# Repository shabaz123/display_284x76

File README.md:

# Display\_284x76

This repository contains KiCad files for an 81 x 29 mm circuit board which contains a 284x76 pixel TFT screen, six buttons and a rotary encoder.

The interface is via either a 20-pin DIL header, or 20-way 1mm-pitch flat flex cable (FFC), to any microcontroller of choice.

The board requires a 5V supply (4.4V to 5.5V should work) at 20 mA for the backlight driver, and a 3.3V 20mA supply for the TFT driver. All signals (SPI and the PWM input) use 3.3V logic levels.

The TFT is part code ER-TFT2.25-1 from BuyDisplay. It contains a ST7789P3 display controller.

# Circuit Diagram

# Pinout

Both the 20-way DIL header and the 20-way FFC connector have the same pinout:

<!-- info: table: widths="13% 87%" -->

| Pin | Description         |
| :-- | :------------------ |
| 1   | GND                 |
| 2   | 5V Input (4.4-5.5V) |
| 3   | SW6'                |
| 4   | SW6                 |
| 5   | SW1                 |
| 6   | SW2                 |
| 7   | SW3                 |
| 8   | SW4                 |
| 9   | SW5                 |
| 10  | ENC\_SW             |
| 11  | ENC\_B              |
| 12  | ENC\_A              |
| 13  | \*TFT\_CS           |
| 14  | TFT\_SCLK           |
| 15  | TFT\_MOSI           |
| 16  | LED\_PWM            |
| 17  | \*TFT\_RESET        |
| 18  | TFT\_D/\*C          |
| 19  | 3.3V Input          |
| 20  | GND                 |

# Enclosure

A possible enclosure is Hammond 1593W. See the front-panel folder for a KiCad project for this example front panel:

M2 spacers of height 6 mm should be suitable for attaching to the display board. 
The button holes are 5.2 mm diameter, which is suitable for "A30 button caps" which are 4.6 mm diameter and intended for B3F-1050 tact switches with a 2.4x2.4 mm square actuator. If you're using different buttons or caps, then you'll likely need to modify the holes in the KiCad files.

# Parts List

<!-- info: table: widths="11% 10% 21% 58%" -->

| Ref     | Qty | Value          | Description                                      |
| :------ | :-- | :------------- | :----------------------------------------------- |
| C1, C2  | 2   | 10n            | Capacitor 0805                                   |
| C3      | 1   | 10u 10V        | Capacitor Tant Case B                            |
| C4-C6   | 3   | 10u 10V        | Capacitor 0805 X7R                               |
| R1-R4   | 4   | 10k            | Resistor 0805                                    |
| R5      | 1   | 47k            | Resistor 0805                                    |
| R6      | 1   | 1k             | Resistor 0805                                    |
| R7      | 1   | 100k           | Resistor 0805                                    |
| R8      | 1   | 20k            | Resistor 0805                                    |
| R9      | 1   | 10R            | Resistor 0805                                    |
| L1      | 1   | 2.2uH          | Inductor 4x4mm 2A 50 mOhm: YNR4026-2R2M          |
| U3      | 1   | TLV62569DBV    | Buck Regulator SOT-23-5                          |
| FB1     | 1   | BLM21AG121SH1D | Ferrite Bead 0805                                |
| ENC1    | 1   | ENC12E         | Rotary Encoder                                   |
| SW1-SW6 | 6   | B3F-1050       | 6x6 B3F or Kailh Mute or E-Switch 5.8x5.8 or 7x7 |
| LCD1    | 1   | ER-TFT2.25-1   | 76x284 ST7789P3 TFT LCD Screen                   |
| LCDCONN | 1   | FFC2B16-08-T   | FPC Top Contact SHOU HAN 0.5-8P CTSJ-H2.0 119    | 
| J1      | 1   | FFC3B11-20-T   | FPC Top Contact GCT 1.0-20P 1mm 20way            | 
| N/A     | 3   | M2 x 6mm       | Hex Spacer 6mm height and M2 6mm screw           |
| N/A     | 1   | Adhesive Foam  | 3.6 mm thick foam for LCD                        |

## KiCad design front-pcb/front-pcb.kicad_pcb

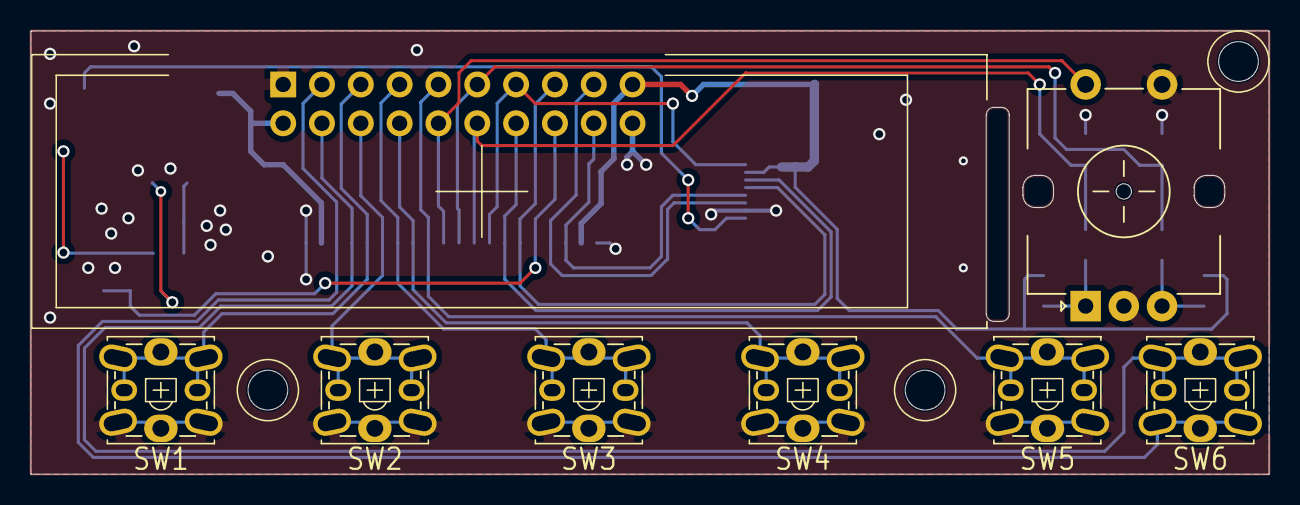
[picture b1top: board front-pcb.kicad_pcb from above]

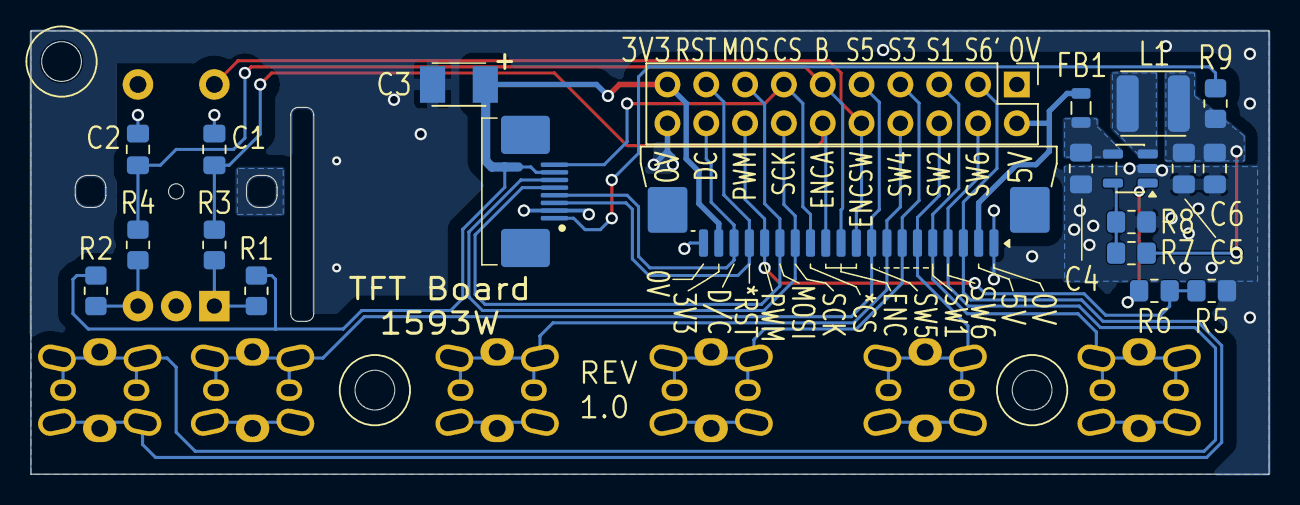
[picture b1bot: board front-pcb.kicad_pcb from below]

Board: 2 copper layers, 81.0 x 29.0 mm, 31 parts (23 on the bottom side), 27 nets.

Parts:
C1, C2: 10n; C_0805_2012Metric_Pad1.18x1.45mm_HandSolder
C3: 10u; Cap-Tant-CaseB
C4, C5, C6: 10u; C_0805_2012Metric_Pad1.18x1.45mm_HandSolder
ENC1: RotaryEncoder; Encoder-and-Switch
FB1: FBEAD; BLM21AG121SH1D
J1: Conn_FPC_20P; FFC_FPC_20P_1mm
J2: Conn_DIL; PinHeader_2x10_P2.54mm_Vertical
L1: 2.2uH; FNR4012S
LCD1: LCD-ER-TFT2.25-1; ER-TFT2.25-1-6mm-reduced-keepout
R1, R2, R3, R4: 10k; R_0805_2012Metric_Pad1.20x1.40mm_HandSolder
R5: 47k; R_0805_2012Metric_Pad1.20x1.40mm_HandSolder
R6: 1k; R_0805_2012Metric_Pad1.20x1.40mm_HandSolder
R7: 100k; R_0805_2012Metric_Pad1.20x1.40mm_HandSolder
R8: 20k; R_0805_2012Metric_Pad1.20x1.40mm_HandSolder
R9: 10R; R_0805_2012Metric_Pad1.20x1.40mm_HandSolder
STANDOFF1, STANDOFF2, STANDOFF3: HOLE-M2-STANDOFF-LOOSEFIT
SW1, SW2, SW3, SW4, SW5, SW6: PUSH-SWITCH; Tact-SW-Kailh-Mute-6x6
U3: TLV62569DBV; SOT-23-5

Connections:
0V: C1.2, C2.2, C3.2, C4.2, C5.2, C6.2, ENC1.C, ENC1.S2, J1.1, J1.20, J2.1, J2.20, LCD1.2 (GND), R5.1, R8.1, SW1.1, SW2.1, SW3.1, SW4.1, SW5.1, U3.2 (GND)
+3.3V: C3.1, J1.19, J2.19, LCD1.7 (VDD), R1.1, R2.1
+5V: FB1.1, J1.2, J2.2
/*TFT_CS: J1.13, J2.13, LCD1.8 (~CS)
/*TFT_RESET: J1.17, J2.17, LCD1.3 (~RESET)
/ENC_A: C1.1, J1.12, J2.12, R3.2
/ENC_B: C2.1, J1.11, J2.11, R4.2
/ENC_SW: ENC1.S1, J1.10, J2.10
/LED_PWM: J1.16, J2.16, R5.2, R6.1
/SW1: J1.5, J2.5, SW1.2
/SW2: J1.6, J2.6, SW2.2
/SW3: J1.7, J2.7, SW3.2
/SW4: J1.8, J2.8, SW4.2
/SW5: J1.9, J2.9, SW5.2
/SW6: J1.4, J2.4, SW6.2
/SW6': J1.3, J2.3, SW6.1
/TFT_D/*C: J1.18, J2.18, LCD1.4 (D/~C)
/TFT_LED_A: LCD1.1 (LED_A), R9.1
/TFT_MOSI: J1.15, J2.15, LCD1.5 (MOSI)
/TFT_SCK: J1.14, J2.14, LCD1.6 (SCK)
unnamed: C5.1, C6.1, L1.2, R7.2, R9.2
unnamed: ENC1.A, R1.2, R3.1
unnamed: ENC1.B, R2.2, R4.1
unnamed: R6.2, U3.1 (EN)
unnamed: R7.1, R8.2, U3.5 (FB)
unnamed: L1.1, U3.3 (SW)
unnamed: C4.1, FB1.2, U3.4 (VIN)
